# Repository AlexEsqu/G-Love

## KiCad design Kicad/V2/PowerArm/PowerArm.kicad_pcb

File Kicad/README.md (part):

https://app.notion.com/p/G-Love-Module-Electronique-06-26-42-Chips-371a25cc104180e3b6d8d438b70a2ca8

# Presentation

[G-Love] est un projet de conception d’un système de vêtement électronique (wearable) porté sur les bras., intégrant des bandes LEDSs RGB réactives à l’environnement et aux mouvements du porteur. (acceleration, flexion, pression)

Le système se présente sous forme de gant relié à une manchette d’avant-bras parcourus de capteurs et de LEDs. Un capteur sur le poignet permet de naviguer entre les modes.

---

# Table des matieres

---

# 1.Manuel d’utilisation

## Interactions

- Sur flexion / pression d’un doigt : animation localisée sur le segment correspondant
- Mouvement brusque du bras : traînée lumineuse, onde ?
- Orientation du bras : dégradé de couleur selon l’axe
- Bonus DMX : LEDs pilotees par reception DMX / Gestion d’une scene en transmission DMX

## Parametrage

- Pression bracelet : changement de mode pour passer d’un preset a l’autre
- Switch : pour demarrer avec ou sans feature LEDs
- Calibrage : via proximite aimant ou combinaison mouvement ?
- Bonus Touchscreen : Changer de mode / couleur

## Demarrage

Un utilisateur devra passer par une étape de calibration pour sa première utilisation du gant (longueur du bras et des doigts, amplitude de mouvement, calibration des senseurs…).
Mais les utilisations suivantes ne devraient pas nécessiter de vraie calibration, placer une nouvelle position d’origine au plus.

## Résumé

Les senseurs du gant devraient permettre de mesurer en temps réel la position de la main dans l’espace, la flexion des doigts, et les contacts avec le bout des doigts.

Les differents capteurs utilisés simultanément devraient permettre a l’utilisateur de déclencher plusieurs effets lumineux sur le display led, avec des combinaisons additives d’effets (mouvement + position des doigts X != mouvement + position Y != mouvement seul)

Ces mesures peuvent aussi être transmises en temps réel à une autre machine (à définir) pour lier ces mesures d’inputs à d’autres effets.

# 2.Features

---

## Mandatory

- 5 Ruban LED adressable sur les doigts, réagissant individuellement
- Interaction sur flexion d’un doigt (capteur flex a chaque doigt)
- Interaction sur pression du bout d’un doigt (capteur pression au bout de chaque doigt)
- Interaction sur :
    - mouvement de la main
    - l’orientation de la main
- Transmission coordonnée dans l’espace en temps réel par UART (précision dans la limite du matériel accessible avec le budget : plusieurs IMU, ou IMU plus précis, balise et triangulation…)
- Surface avant-bras LED adressable 16x16 / 16x64 (dans limite budget)
- Interaction sur l’avant bras (capteur pression)
- Envoi des donnees en USB via bridge USB to UART
- Système de reset des positions/mouvements (simple bouton ou combinaison d’input). Peut être nécessaire suivant le fonctionnement du capteur et la longueur d’utilisation.
- Système de calibration capable définir nouvelle origine (point 0,0,0) , sans reset tout le système. (si la calibration a été faite, un reset complet de la machine peut etre rattrappe en 2secondes si l’utilisateur garde une position de repos)

    Définir amplitude max du bras (bras tendu, leve, a plat sur les cuisses)

- Gestion embarquée de la chaleur des LEDs par capteur température et optimisation software ; utiliser des techno type textile conducteur, ??? pour permettre PLUS DE LED

## Bonus

#### Communication

- Interaction entre 2 gants dans le meme espace via coordonnees transmises en USB

#### TouchScreen

- Bonus: Touchscreen ou autre système d’input pour changer de mode/paramètres.

    Peut etre utile pour changer plus facilement les options pendant l‘utilisation de l’objet. Et pour visualiser les paramètres actuels sans trop perturber le display principal de l’objet.

#### DMX

- Bonus: Transmission DMX via driver RS-485 (MAX485 + XLR DMX)

    +Note: émission de format DMX probablement ingérable, réception semble plus réaliste.

#### FingerTip

- Bonus: Module Plug and Play HEARTBEAT capteur de pouls
- Bonus: Module Plug and play PISTODOIGT en infrarouge pour jouer au laser tag avec un doigt canon et le flex d’un autre doigt pour la gâchette  🔫
- Super Bonus : Module Plug and Play CURSOR permettant de dessiner en 3D ; Captation suffisamment précise pour dessiner un 42 lisible dans l’espace d’un 1m3

---

# 3. Schema fonctionnel

!Schema Fonctionnel.png

TO DO:
- formes logique
- légende
- ajouter ref compo

---

# 4. Matériel et protocoles

- **Microcontrôleurs relies UART** :
    - ATmega328P
    - ATmega32U4 (1 controleur principal pour les gouverner tous)
- **Bandes LEDs RGB** : WS2812B ou APA102 le long des doigts et panneau LEDs sur l’avant-bras
- **Capteurs** :

    **ADC** protocole **: Flex sensors** pour la flexion (duh), **FSR** (force-sensing resistor) pour la pression des doigts via multiplexeur CD4067

    **SPI / I2c** protocole **: IMU** (inertial measurement unit) pour accéléromètre + gyroscope,

    **Proximité** : Capteur Hall digital A3144

- **Support** : PCB Flex et PCB rigides avec segments flexibles entre chaque
- **Microcontrôleurs relies en UART** :
    - **ATmega328P (**main**)**
    - **ATmega2561** (avant-bras)
- **Capteurs** :

    **ADC** via multiplexer CD4067 **:**

    - **Flex sensors** pour la flexion des doigts
    - **FSR** (force-sensing resistor) pour la pression des doigts

    **I2C : IMU** (inertial measurement unit) pour accéléromètre + gyroscope

    **Digital I/O** :

    - **Capteur** Hall digital A3144
    - **bandes LEDs RGB** APA102 le long des doigts et panneau LEDs sur l’avant-bras
- **HeatSensor :** Utilisation de Thermistance NTC (negative temperature coefficient = la résistance diminue lorsque la température augmente), placé là où il y a le plus de variation de chaleur possible (rubans LED) avec de la colle thermique pour mieux capté la chaleur et recouvert d’un ruban Kapton pour isolé de l’air ambiant

- **Bonus SPI/I2C** : touchscreen, **GC9A01** est la puce qui contrôle l'affichage de l'écran et communique en SPI et **CST816D** est la puce qui contrôle la détection du tactile, communique en I2C
    - En sortie (Affichage - GC9A01) :
        - Afficher le mode d'interaction actuel (ex: "Mode DMX", "Mode Laser Tag")
        - Afficher des retours visuels lors de l'étape de calibration
    - En entrée (Saisie tactile - CST816D) :
        - Changement de mode: changement de mode pour différent interaction prédefini
        - Parametrage de couleurs: afficher une roue chromatique sur l'écran, permettant à l'utilisateur de sélectionner directement au doigt la couleur de base de ses bandes LED.
        - Bouton de secours / de reset: permet de déclencher manuellement un recalibration ou un “reset” en appuyant sur un bouton
- **Bonus UART** : USB
- **Bonus UART** : DMX
- **Support** : PCB Flex et PCB rigides avec segments flexibles entre chaque

## SPI (**Serial Peripheral Interface**)

SPI est un protocole ultra-rapide avec 4 fils : MOSI, MISO, SCK, CS. Fonctionnant sur une architecture de type master/slave, il permet des transferts de données bidirectionnels simultanenent  sans ralentir le microcontrôleur principal.

La synchronisation des échanges est assuré par un signal d’horloge généré exclusivement par le microcontroleur configuré en maitre

Le bus SPI repose sur l’utilisation de quatre lignes de signaux:

- SCK(Serial Clock) : Signal d’horloge generé par le maitre, il cadence le rythme de transmission des bits de données
- MOSI(Master Out Slave In) : Ligne de données unidirectionelle transportant les informations du maitre vers le slave
- MISO(Master In Slave Out) : ligne de données unidirectionelle transportant les informations du slave vers le maitre
- CS / SS (Chip Select / Slave Select) : Ligne d’activation dédié a chaque composant esclave, ce signal est actif a l’etat bas (0V), tant que le signal d’un esclave est haut, celui ci ignore le bus SPI et libere la ligne MISO
- Composant : Ruban LED APA102 (avant-bras).
    - **Le Maître :** L'ATmega328P est le maître du bus SPI
    - **Esclave :** Bandes LEDs APA102
    - **L'Usage :** Mise à jour à très haute fréquence de la matrice visuelle de l'avant-bras
    - **Câblage** : Utilise le D11(MOSI - Données) et D13 (SCK - Horloge)
- Composant : Ecran GC9A01
    - **Le Maitre** : L’ATMega2561 est le maitre du bus SPI
    - **Esclave :** L’écran GC9A01,
    - **L'Usage :** Le protocole SPI est un protocole assez rapide pour travailler et rafraichir un écran de 240x240pixels
    - **Cablage** : PB1(SCK - Horloge), PB2 (MOSI - Données), PB0 (SS/CS - Selection de l’ecran)

Les LED WS2812B utilise un protocole propriétaire de communication monofil, l’envoi des données à ces LED peut bloquer l’execution du programme et desactive les interruption du microcontrolleur

En choisissant les LED APA102 fonctionnant en SPI, la transmission de données est cadencée par la ligne d’horloge matérielle (SCK).  L’ATMega328P peut rafraichir l’affichage des LED sans aucune contrainte de temps grace au protocole SPI, lui permettant de simultanément et sans latences les capteurs

L’utilisation du protocole SPI pour l’affichage de l’ecran du TouchScreen permet aussi d’atteindre un taux de rafaichissement d’écran plus élevé et fluide avec 8MHz avec l’atm2561 contre 400kHz en I2C

## I2C **(Inter-Integrated Circuit)**

Le protocole I2C est un standard de communication bidirectionnel, il repose sur un principe d’adressage logiciel et permet de facilement reliée un microcontrolleur et différents circuits.

Contrairement au SPI qui necessite une ligne individuelle (Chip Select) par peripherique, le protocole I2C permet de connecter plusieurs dizaines de composants en parallele sur seulement deux lignes de communication:

- SCL (Serial Clock) : Signal d’horloge generé par le maitre pour cadencer la transmission des bits
- SDA (Serial Data) : Ligne de données bidirectionnelle transportant alternativement les informations du maitre vers le slave, et du slave vers le maitre

Adressage Unique: Chaque esclave I2C possède une adresse codée en binaire définie en usine ou par configuration matérielle. Le maitre commence chaque interaction en envoyant l’adresse du composant visé sur le fil SDA. Seul le composant possédant cette adresse répond, les autres ignorant la suite des paquets.

- Composant : ICM-42699-P
    - **Le Maitre** : L’ATMega328P est le maitre du bus I2C
    - **Esclave :**  ICM-42699-P
    - **L'Usage :** Le protocole I2C est
    - **Cablage** : SDA et SDL
- Composant : ecran tactile CST816D
    - **Le Maitre** : L’ATMega2561 est le maitre du bus I2C
    - **Esclave :**  CST816D
    - **L'Usage :** Le protocole I2C est
    - **Cablage** : SDA et SDL

L’adoption de l’I2C pour la gestion des capteurs de position et l’interaction tactile du TouchScreen:

- Minimisation de l’encombrement du cablage
    - L’I2C permet de connecter l’IMU et l’ecran tactile en n’utilsaint que 2 lignes de données, evitant de saturer les pins des micronctrolleur et d’alourdir le cablage flexible du bras
- Echange de données plus lent
    - Contraireemnt à l’écran LCD, le tactile et l’IMU ne transmettenet que de petit paquets de données, la vitesse de l’I2C est suffisante pour l’echange de donnée

## UART (Universal Asynchronous Receiver-Transmitter)

## ADC

## DIGITAL I/O

---

# 5. Pinout

## ATmega328p — Concentrateur capteurs + APA102

### MANDATORY

#### ALIMENTATION & PROGRAMMATION

| Pin | Composant | Signal / rôle | Protocole |
| --- | --- | --- | --- |
| **VCC / GND** | Alim | 5V — 100nF par paire VCC/GND | PWR |
| **RESET** | Reset | Pull-up 10kΩ vers VCC | Reset |

---

#### CRYSTAL OSCILLATOR

| Pin | Composant | Signal / rôle | Protocole |
| --- | --- | --- | --- |
| **B6 / XTAL1** | Crystal / Oscillator | External Clock |  |
| **B7 / XTAL2** | Crystal / Oscillator | External Clock |  |

---

#### ADC + MULTIPLEXER

| Pin | Composant | Signal / rôle | Protocole |
| --- | --- | --- | --- |
| **C0** | CD4067 S0 | Sélection canal multiplexeur | Digital |
| **C1** | CD4067 S1 | Sélection canal multiplexeur | Digital |
| **C2** | CD4067 S2 | Sélection canal multiplexeur | Digital |
| **C3** | CD4067 S3 | Sélection canal multiplexeur | Digital |
| **ADC7** | CD4067 output | Multiplex FSR doigts + Flex | ADC |
| **ADC6** | FSR 402 poignet | Capteur de force | ADC |

---

#### I2C IMU

| Pin | Composant | Signal / rôle | Protocole |
| --- | --- | --- | --- |
| **C4 / SDA** | ICM-42688 | IMU SDA | I2C |
| **C5 / SCL** | ICM-42688 | IMU SCL | I2C |

---

#### GPIO Hall

| Pin | Composant | Signal / rôle | Protocole |
| --- | --- | --- | --- |
| **D6** | A3144 Hall | Capteur magnétique | GPIO |

---

#### SPI LEDs

| Pin | Composant | Signal / rôle | Protocole |
| --- | --- | --- | --- |
| **B4** | APA102 ruban #1 | CS ruban 1 | GPIO CS |
| **B3 / MOSI** | APA102 DI (tous) | Data SPI — bus commun | SPI HW |
| **B5 / SCK** | APA102 CI (tous) | Clock SPI — bus commun | SPI HW |

---

#### BONUS UART

| Pin | Composant | Signal / rôle | Protocole |
| --- | --- | --- | --- |
| **D0 / RX** | ATmega2561 | RX ← TX du 2561 | UART |
| **D1 / TX** | ATmega2561 | TX → RX du 2561 | UART |

---

#### RECAP

| Pin | Composant | Signal / rôle | Protocole |
| --- | --- | --- | --- |
| **C0** | CD4067 S0 | Sélection canal multiplexeur | Digital |
| **C1** | CD4067 S1 | Sélection canal multiplexeur | Digital |
| **C2** | CD4067 S2 | Sélection canal multiplexeur | Digital |
| **C3** | CD4067 S3 | Sélection canal multiplexeur | Digital |
| **ADC7** | CD4067 output | Multiplex FSR doigts + Flex | ADC |
| **D6** | A3144 Hall | Capteur magnétique | Digital IN |
| **B4** | APA102 ruban #1 | CS ruban 1 | GPIO CS |
| **B3 / MOSI** | APA102 DI (tous) | Data SPI — bus commun | SPI HW |
| **B5 / SCK** | APA102 CI (tous) | Clock SPI — bus commun | SPI HW |
| **ADC6** | FSR 402 poignet | Capteur de force | ADC |
| **C4 / SDA** | ICM-42688 | IMU SDA | I2C |
| **C5 / SCL** | ICM-42688 | IMU SCL | I2C |
| **B6 / XTAL1** | Crystal / Oscillator | External Clock |  |
| **B7 / XTAL2** | Crystal / Oscillator | External Clock |  |
| **VCC / GND** | Alim | 5V — 100nF par paire VCC/GND | PWR |
| **RESET** | Reset | Pull-up 10kΩ vers VCC | Reset |

| **D0 / RX** | ATmega2561 | RX ← TX du 2561 | UART |
| --- | --- | --- | --- |
| **D1 / TX** | ATmega2561 | TX → RX du 2561 | UART |

---

## BONUS A FINIR

## ATmega2561 — Display + bus + périphériques

#### ALIMENTATION & PROGRAMMATION

| Pin | Composant | Signal / rôle | Protocole |
| --- | --- | --- | --- |
| **VCC / GND** | Alim | 5V — 100nF par paire VCC/GND | PWR |
| **RESET** | Reset | Pull-up 10kΩ vers VCC | Reset |

---

#### CRYSTAL OSCILLATOR

| Pin | Composant | Signal / rôle | Protocole |
| --- | --- | --- | --- |
| **XTAL1** | Crystal / Oscillator | External Clock |  |
| **XTAL2** | Crystal / Oscillator | External Clock |  |

#### UART0 — Lien vers ATmega328p

| Pin | Composant | Signal / rôle | Protocole |
| --- | --- | --- | --- |
| **E0** | ATmega328p | RX ← TX du 328p | UART0 |
| **E1** | ATmega328p | TX → RX du 328p | UART0 |

#### UART1 — USB via FTDI FT232R / Bus RS-485 via MAX487

| Pin | Composant | Signal / rôle | Protocole |
| --- | --- | --- | --- |
| **D2 / TXD2** | 74HC4053 | TX → FTDI RX / MAX487 DI | UART1 |
| **D3 / RXD2** | 74HC4053 | RX ← FTDI TX (1kΩ série) / MAX487 RO | UART1 |
| **D5** | 74HC4053 | Switch Digital | GPIO |
| **D4** | GPIO | MAX487 DE + ~RE (liés ensemble) | GPIO |

#### **Module TouchScreen (GC9A01 + CST816D) avec LevelShifter TXS0108EPWR**

| Pin | Composant | Signal / rôle | Protocole |
| --- | --- | --- | --- |
| PB0 | ~SS / CS | LCD CS | GPIO CS |
| PB1 | SCK | SCLK | SPI |
| PB2 | MOSI | MOSI | SPI |
| PB3 | MISO | MISO | SPI |
| PB4 | GPIO | LCD DC / RS | GPIO |
| PB5 | GPIO | LCD RST | GPIO |
| PD0 | SCL I2C | Touchscreen SCL | I2C |
| PD1 | SDA I2C | Touchscreen Data | I2C |
| PE4 | INT4 | Touchscreen Interrupt | I2C |

#### Plug & play (pouls / IR) + switch pression

| Pin | Composant | Signal / rôle | Protocole |
| --- | --- | --- | --- |
| **PE2** | INT2 | Capteur pouls / IR — signal data | INT ext. |
| **PE3** | GPIO | Détection présence connecteur (pull-up) | GPIO |
| **PE4** | INT4 | Switch pression — interrupt | INT ext. |

# 6. BOM

| Component | QTY | Prix unitaire (€) | Prix total (€) | Fournisseur |
| --- | --- | --- | --- | --- |
| **ATMega328P** | 1 | 2,26 | 2,26 | https://www.digikey.fr/fr/products/detail/microchip-technology/ATMEGA328P-AU/1832260 |
| **ATMega2561** | 1 | 13,17 | 13,17 | https://www.digikey.fr/fr/products/detail/microchip-technology/ATMEGA2561-16AU/735457 |
| **Interlink FSR 400 short (FSR doigt)** | 5 | 4,886 | 24,43 | https://www.digikey.fr/fr/product-highlight/i/interlink/fsr-400-round-force-sensing-resistor |
| **Spectra Symbol SEN-10264 2.2” (Flex Sensor)** | 4 | 10,16 | 40,64 | https://www.digikey.fr/fr/products/detail/sparkfun-electronics/10264/17829611 |
| **Interlink FSR 402 medium (FSR avant bras)** | 1 | 6,05 | 6,05 | https://www.digikey.fr/en/product-highlight/i/interlink/fsr-402-round-force-sensing-resistor |
| **Multiplexer CD4067**  | 1 | 0,79 | 0,79 | https://www.digikey.fr/fr/products/detail/texas-instruments/CD4067BM96/1691267 |
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
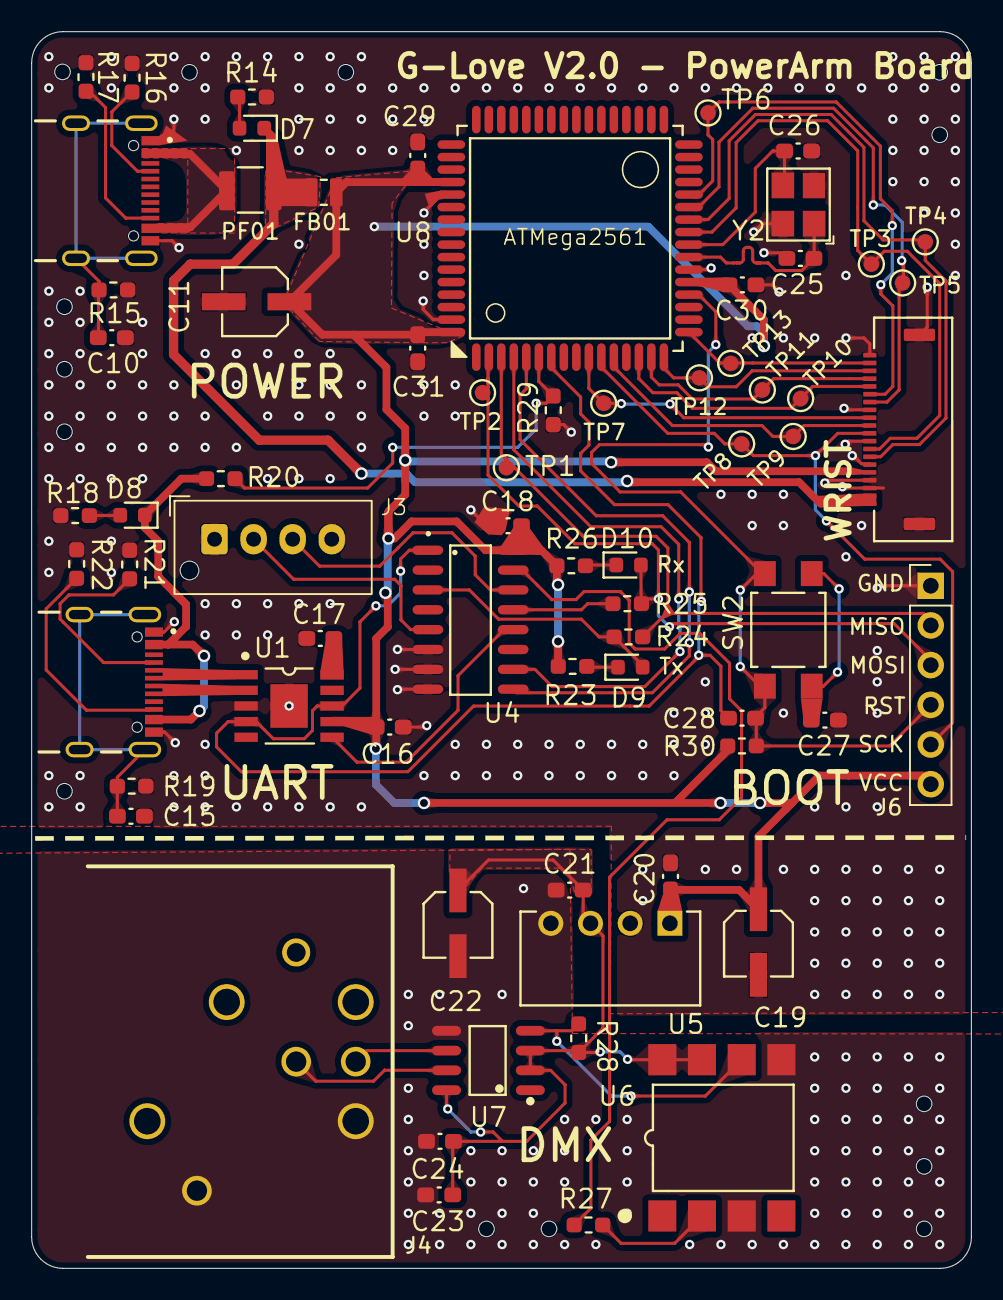
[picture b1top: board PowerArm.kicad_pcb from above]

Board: 2 copper layers, 60.1 x 79.1 mm, 69 parts (0 on the bottom side), 50 nets.

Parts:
C10: 10n; Capacitor_0603
C11, C19, C22: 4.7uF; Capacitor_Electrolytic
C15: 10nF; Capacitor_0603
C16, C17, C18, C20, C21, C23, C24, C27, C28, C29, C30, C31: 100nF; Capacitor_0603
C25, C26: 12pF; Capacitor_0603
D7: RED; LED
D8: GREEN; LED
D9, D10: YELLOW; LED
FB01: FERRITE BEAD
J1: JST_Connector_To_Wrist_Board; conn_zif_20x0.5mm
J2: USB Connector to Computer; USB_C_Receptacle_GCT_USB4105-xx-A_16P_TopMnt_Horizontal
J3: JST_Connector_To_Other_Glove; Conn_JST_4x2.50mm
J4: XLR5_Ground; XLR5_Connector_Female_CONN-TH_NC5FAH
J5: USB Connector to Powerbank; USB_C_Receptacle_GCT_USB4105-xx-A_16P_TopMnt_Horizontal
J6: PinHeader_1x06_P2.54mm_Vertical
PF01: POLYMER FUSE
R14, R18, R20, R23, R24, R25, R26: 1k; Resistor_0603
R15, R19: 1M; Resistor_0603
R16, R17: 5.1k; Resistor_0603
R21, R22: 5.1K; Resistor_0603
R27: 330R; Resistor_0603
R28: 4.7k; Resistor_0603
R29: 10k; Resistor_0603
R30: 10kΩ; Resistor_0603
SW2: SW_SPST_TL3305A
TP1, TP2, TP3, TP4, TP5, TP6, TP7, TP8, TP9, TP10, TP11, TP12, TP13: TestPoint_Pad_D1.0mm
U1: CH340K
U4: 74HC4052
U5: B0505S-1W1; B0505S
U6: 6N137
U7: MAX485E; MAX485ED
U8: ATMEGA2561-16AU; ATMega2561
Y2: 16MHz; Crystal_16MHz

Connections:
/ATMega2561/2561_MOSI: J1.11 (MOSI), TP9.1, U8.12 ((MOSI/PCINT2)_PB2)
/ATMega2561/2561_MUX_SELECT_A: U4.10 (A), U8.4 (PE2_(XCK0/AIN0))
/ATMega2561/2561_MUX_SELECT_B: U4.9 (B), U8.5 (PE3_(OC3A/AIN1))
/ATMega2561/2561_RXD1: J1.14 (2561_RX), TP5.1, U8.27 ((RXD1/INT2)_PD2)
/ATMega2561/2561_SCL: J1.8 (SCL), TP3.1, U8.25 ((SCL/INT0)_PD0)
/ATMega2561/2561_SCREEN_DC: J1.16 (SCREEN_DC), TP10.1, U8.14 ((OC2A/_PCINT4)_PB4)
/ATMega2561/2561_SCREEN_RESET: J1.17 (SCREEN_RESET), TP11.1, U8.15 ((OC1A/PCINT5)_PB5)
/ATMega2561/2561_SDA: J1.7 (SDA), TP4.1, U8.26 ((SDA/INT1)_PD1)
/ATMega2561/2561_SS: J1.12 (SS), TP7.1, U8.10 ((~SS/PCINT0)_PB0)
/ATMega2561/2561_TOUCH_INT: J1.18 (TOUCH_INT), TP12.1, U8.16 ((OC1B/PCINT6)_PB6)
/ATMega2561/2561_TOUCH_RESET: J1.19 (TOUCH_RESET), TP13.1, U8.17 ((OC0A/OC1C/PCINT7)_PB7)
/ATMega2561/2561_TXD1: J1.15 (2561_TX), TP6.1, U8.28 ((TXD1/INT3)_PD3)
/ATMega2561/2561_USB1_INT: R20.2, R29.2, U8.6 (PE4_(OC3B/INT4))
/ATMega2561/DTR: C28.2, U1.4 (~DTR), U1.8 (TXD), U4.1 (Y0), U8.7 (PE5_(OC3C/INT5))
/ATMega2561/MCU_2561_RESET: C28.1, J6.4, R30.1, SW2.2, U8.20 (~RESET)
/ATMega2561/MISO_BOOT_2561: J6.2, R24.2, TP1.1, U8.3 (PE1_(TXD0/PDO))
/ATMega2561/MOSI_BOOT_2561: D10.2 (K), J6.3, R25.2, TP2.1, U8.2 (PE0_(RXD0/PCINT8/PDI))
/ATMega2561/SCK_BOOT_2561: J1.10 (SCK), J6.5, TP8.1, U8.11 ((SCK/PCINT1)_PB1)
/Data/DMX/TX_DMX: R27.1, U4.15 (X2)
GND: C10.2, C11.2, C15.2, C16.1, C17.1, C18.2, C19.2, C20.2, C25.2, C26.1, C27.1, C29.2, C30.2, C31.2, J1.3 (GND), J1.4 (GND), J1.6 (GND), J1.9 (GND), J1.13 (GND), J1.20 (GND), J3.1 (GND), J3.4 (GND), J6.1, R14.1, R15.2, R16.1, R17.1, R18.1, R19.2, R21.2, R22.2, R29.1, U1.3 (GND), U1.11 (GND), U4.6 (INH), U4.7 (VEE), U4.8 (GND), U5.2 (GND), U8.22 (GND_2), U8.53 (GND), U8.63 (GND_3), Y2.2 (G), Y2.4 (G)
unnamed: C27.2, SW2.1
unnamed: D7.2 (K), R14.2
unnamed: D8.2 (K), R18.2
unnamed: D9.1 (A), R23.2
unnamed: D9.2 (K), R24.1, U4.3 (Y)
unnamed: D10.1 (A), R26.2
unnamed: J2.A5 (CC1), R21.1
unnamed: J2.B5 (CC2), R22.1
unnamed: C15.1, J2.SH (SHIELD), R19.1
unnamed: J3.3 (Rx), U4.14 (X1)
unnamed: J3.2 (Tx), U4.5 (Y1)
unnamed: C21.2, C22.2, C23.1, C24.1, J4.1, J4.G, U5.4 (0V), U6.3 (C), U6.5 (GND), U7.5 (GND)
unnamed: J4.2, U7.7 (B)
unnamed: J5.A5 (CC1), R16.2
unnamed: J5.B5 (CC2), R17.2
unnamed: C10.1, J5.SH (SHIELD), R15.1
unnamed: U1.6 (RXD), U4.12 (X0)
unnamed: J2.A6 (D-), J2.B7 (D-), U1.1 (UD+)
unnamed: J2.A7 (D+), J2.B6 (D+), U1.2 (UD-)
unnamed: C17.2, U1.10 (V3)
unnamed: R25.1, U4.13 (X)
unnamed: C21.1, C22.1, C23.2, C24.2, R28.2, U5.3 (+VO), U6.7 (EN), U6.8 (VCC), U7.2 (~RE), U7.3 (DE), U7.8 (VCC)
unnamed: R27.2, U6.2 (A)
unnamed: R28.1, U6.6 (VO), U7.4 (DI)
unnamed: J4.3, U7.6 (A)
unnamed: C26.2, U8.24 (XTAL1), Y2.3
unnamed: C25.1, U8.23 (XTAL2), Y2.1
VBUS: D8.1 (A), PF01.1, R20.1
VCC: C11.1, C16.2, C18.1, C19.1, C20.1, C29.1, C30.1, C31.1, FB01.2, J1.5 (5V), J6.6, R23.1, R26.1, R30.2, U1.7 (VCC), U4.16 (VCC), U5.1 (VIN), U8.21 (VCC_2), U8.52 (VCC), U8.64 (AVCC)
VCCL: D7.1 (A), FB01.1, J1.1 (5V_LED), J1.2 (5V_LED), PF01.2

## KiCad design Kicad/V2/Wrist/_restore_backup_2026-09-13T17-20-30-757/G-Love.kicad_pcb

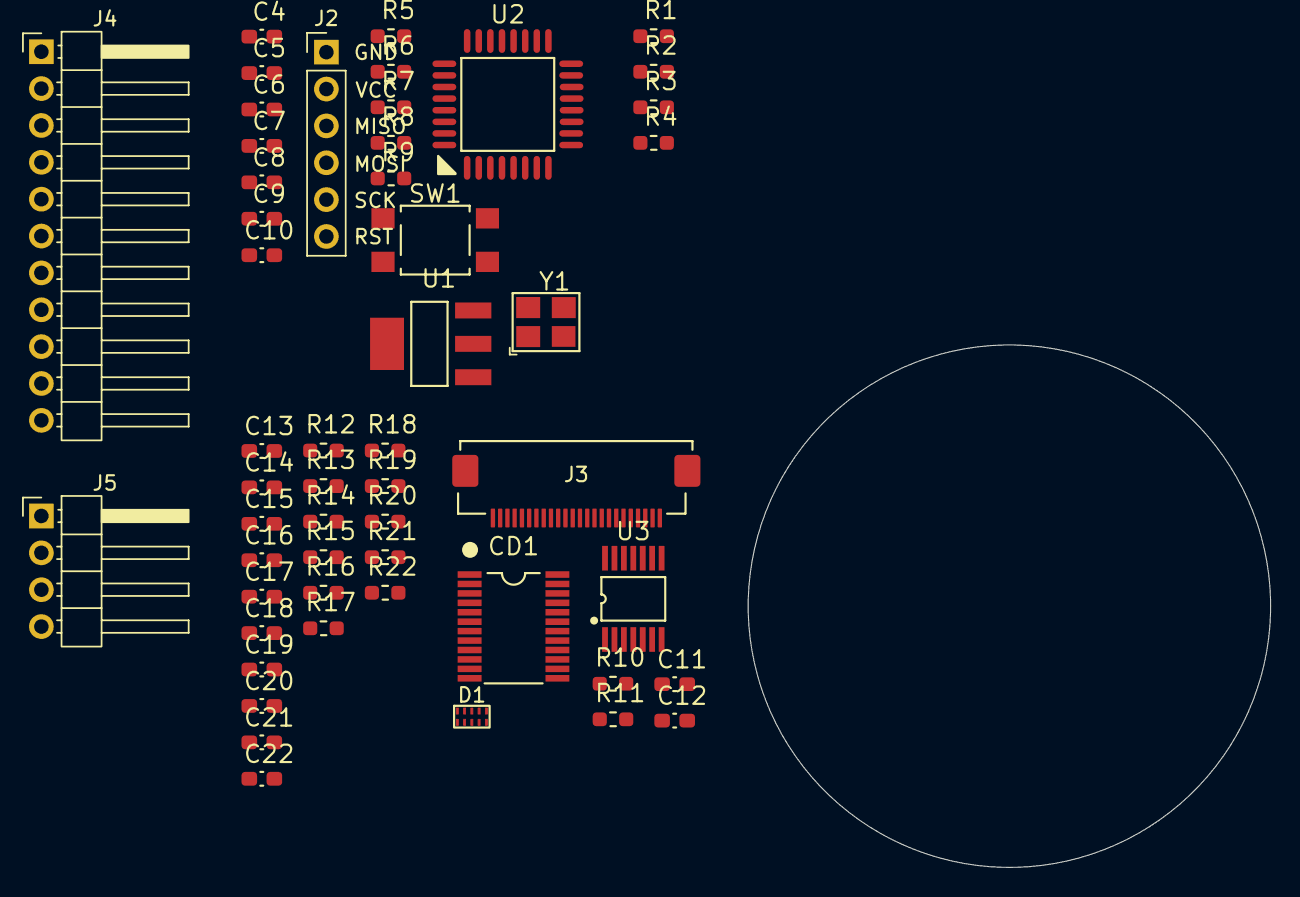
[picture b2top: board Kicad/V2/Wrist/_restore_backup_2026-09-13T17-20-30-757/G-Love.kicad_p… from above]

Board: 2 copper layers, 36.0 x 36.0 mm, 52 parts (0 on the bottom side), 37 nets, no tracks yet.

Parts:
C4, C5, C6, C7, C8, C11, C12: 100nF; Capacitor_0603
C9, C10: 12pF; Capacitor_0603
C13, C14, C15, C16, C17, C18, C19, C20, C21, C22: 10nF; Capacitor_0603
CD1: CD4097B
D1: TVS_DIODE
J2: PinHeader_1x06_P2.54mm_Vertical
J3: FPC_CONNECTOR_24
J4: PinHeader_1x11_P2.54mm_Horizontal
J5: PinHeader_1x04_P2.54mm_Horizontal
R1, R2, R8, R9: 2.2kΩ; Resistor_0603
R3, R4, R10, R11: 2.2K; Resistor_0603
R5, R13, R14, R15, R16, R17, R18, R19, R20, R21, R22: 10kΩ; Resistor_0603
R6, R7: 330R; Resistor_0603
R12: 10K; Resistor_0603
SW1: SW_SPST_TL3305A
U1: AMS1117
U2: ATMega328P; ATMega328P-AU
U3: TXS0104E; TXS0104EPWR
Y1: 16MHz; Crystal_16MHz

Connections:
+3.3V: C12.2, J3.8 (3.3V), J5.1, R10.2, R11.2, U1.2 (Vout), U3.1 (V_{CCA})
/ATmega328p/328P_ADC_MUX_INH: CD1.13 (INHIBIT), U2.26 (ADC3/PCINT11/PC3)
/ATmega328p/328P_ADC_MUX_SELECT_A: CD1.10 (A), U2.25 (ADC2/PCINT10/PC2)
/ATmega328p/328P_ADC_MUX_SELECT_B: CD1.11 (B), U2.23 (ADC0/PCINT8/PC0)
/ATmega328p/328P_ADC_MUX_SELECT_C: CD1.14 (C), U2.24 (ADC1/PCINT9/PC1)
/ATmega328p/328P_ADC_X_OUT: CD1.1 (X_OutIn), U2.22 (ADC7)
/ATmega328p/328P_ADC_Y_OUT: CD1.17 (Y_OutIn), U2.19 (ADC6)
/ATmega328p/328P_I2C_IMU_SCL: R4.1, R8.1, U2.28 (SCL/ADC5/PCINT13/PC5), U3.12 (B2)
/ATmega328p/328P_I2C_IMU_SDA: R3.1, R9.1, U2.27 (SDA/ADC4/PSCINT12/PC4), U3.13 (B1)
/ATmega328p/MCU_328P_RESET: J2.4, R5.1, SW1.2, U2.29 (~RESET/PCINT14/PC6)
/ATmega328p/MISO_BOOT_328P: D1.2, J2.2, J3.5 (MOSI), R6.2
/ATmega328p/MOSI_BOOT_328P: J2.3, U2.16 (MISO/PCINT4/PB4)
/ATmega328p/SCK_BOOT_328P: D1.1, J2.5, J3.6 (SCK), R7.2
/FingerTip Modules/FingerTip_I2C_SCL: J4.5, J5.2, R1.1
/FingerTip Modules/FingerTip_I2C_SDA: J4.4, J5.3, R2.1
/Hand_Captors/hand_captors/FLEX_INDEX_IN: C16.1, CD1.8 (X_1), J3.16 (FLEX_INDEX), R16.1
/Hand_Captors/hand_captors/FLEX_LITTLE_IN: C22.1, CD1.5 (X_4), J3.23 (FLEX_LITTLE), R22.1
/Hand_Captors/hand_captors/FLEX_MIDDLE_IN: C18.1, CD1.7 (X_2), J3.19 (FLEX_MIDDLE), R18.1
/Hand_Captors/hand_captors/FLEX_RING_IN: C20.1, CD1.6 (X_3), J3.21 (FLEX_RING), R20.1
/Hand_Captors/hand_captors/FLEX_THUMB_IN: C14.1, CD1.9 (X_0), J3.14 (FLEX_THUMB), R14.1
/Hand_Captors/hand_captors/FORCE_INDEX_IN: C15.1, CD1.22 (Y_1), J3.15 (FSR_INDEX), R15.1
/Hand_Captors/hand_captors/FORCE_LITTLE_IN: C21.1, CD1.19 (Y_4), J3.22 (FORCE_LITTLE), R21.1
/Hand_Captors/hand_captors/FORCE_MIDDLE_IN: C17.1, CD1.21 (Y_2), J3.17 (FSR_MIDDLE), R17.1
/Hand_Captors/hand_captors/FORCE_RING_IN: C19.1, CD1.20 (Y_3), J3.20 (FORCE_RING), R19.1
/Hand_Captors/hand_captors/FORCE_THUMB_IN: C13.1, CD1.23 (Y_0), J3.13 (FSR_THUMB), R13.1
/Hand_Captors/hand_captors/HALL_IN: CD1.18 (Y_5), J3.12 (SW_HALL), R12.1
GND: C4.1, C5.1, C6.1, C7.1, C8.2, C9.1, C10.1, C11.2, C12.1, C13.2, C14.2, C15.2, C16.2, C17.2, C18.2, C19.2, C20.2, C21.2, C22.2, CD1.12 (VSS), D1.3, J2.1, J3.3 (GNDL), J3.4 (GNDL), J3.7 (GND), J3.11 (GND), J3.18 (GND), J3.24 (GND), J4.1, J5.4, R13.2, R14.2, R15.2, R16.2, R17.2, R18.2, R19.2, R20.2, R21.2, R22.2, U1.1 (GND), U2.3 (GND), U2.5 (GND), U2.21 (GND), U3.7 (GND), Y1.2 (G), Y1.4 (G)
unnamed: C7.2, SW1.1
unnamed: D1.5, J3.10 (SCL), R10.1, U3.3 (A2)
unnamed: D1.4, J3.9 (SDA), R11.1, U3.2 (A1)
unnamed: C4.2, U2.20 (AREF)
unnamed: R6.1, U2.15 (OC2A/MOSI/PCINT3/PB3)
unnamed: R7.1, U2.17 (SCK/PCINT5/PB5)
unnamed: C9.2, U2.7 (XTAL1/TOSC1/PCINT6/PB6), Y1.1
unnamed: C10.2, U2.8 (XTAL2/TOSC2/PCINT7/PB7), Y1.3
VCC: C5.2, C6.2, C8.1, C11.1, CD1.24 (VDD), J2.6, J4.11, R1.2, R2.2, R3.2, R4.2, R5.2, R8.2, R9.2, R12.2, U1.3 (Vin), U2.4 (VCC), U2.6 (VCC), U2.18 (AVCC), U3.14 (V_{CCB})
VCCL: J3.1 (VCCL), J3.2 (VCCL)

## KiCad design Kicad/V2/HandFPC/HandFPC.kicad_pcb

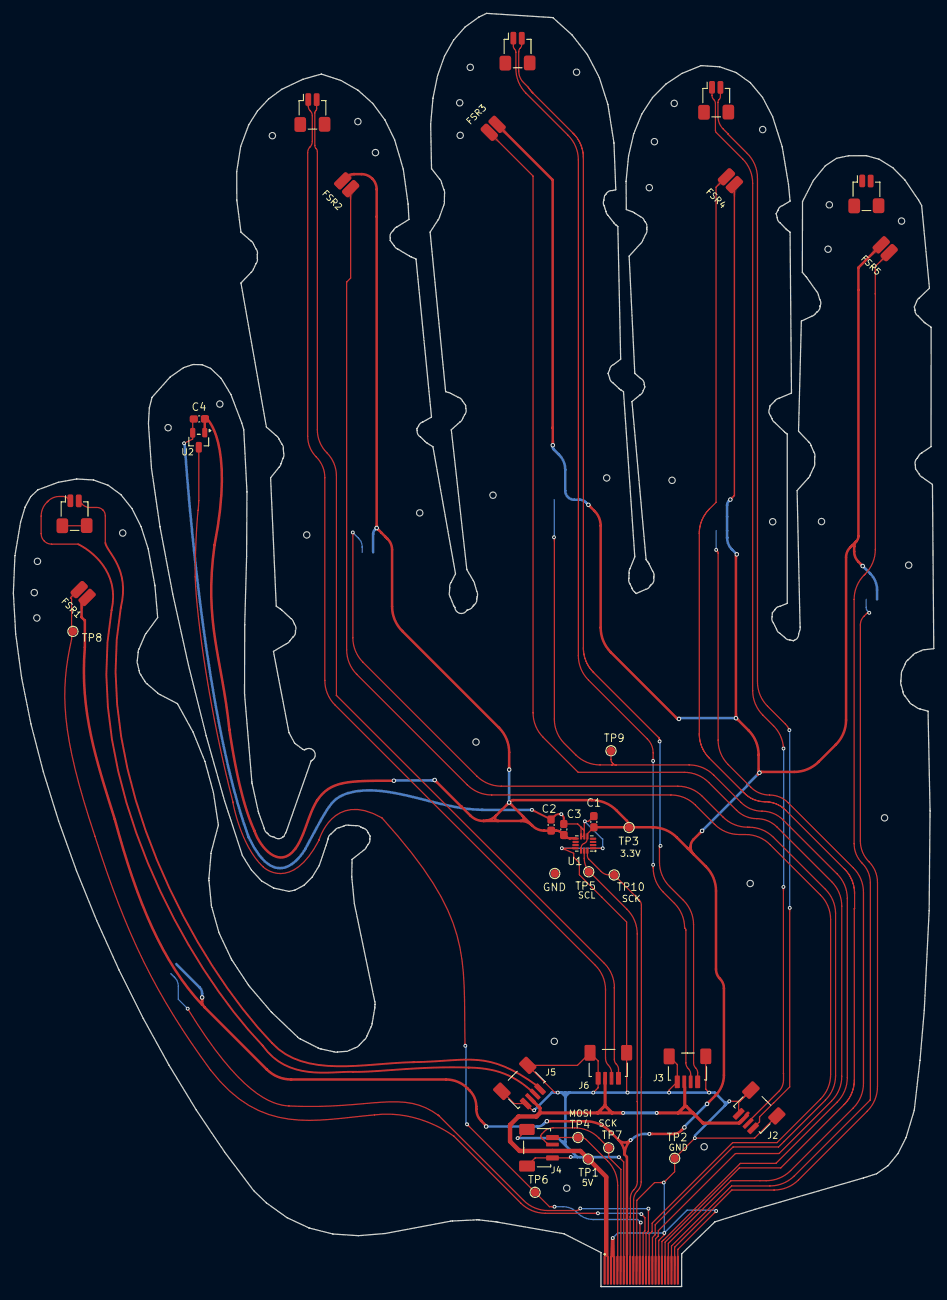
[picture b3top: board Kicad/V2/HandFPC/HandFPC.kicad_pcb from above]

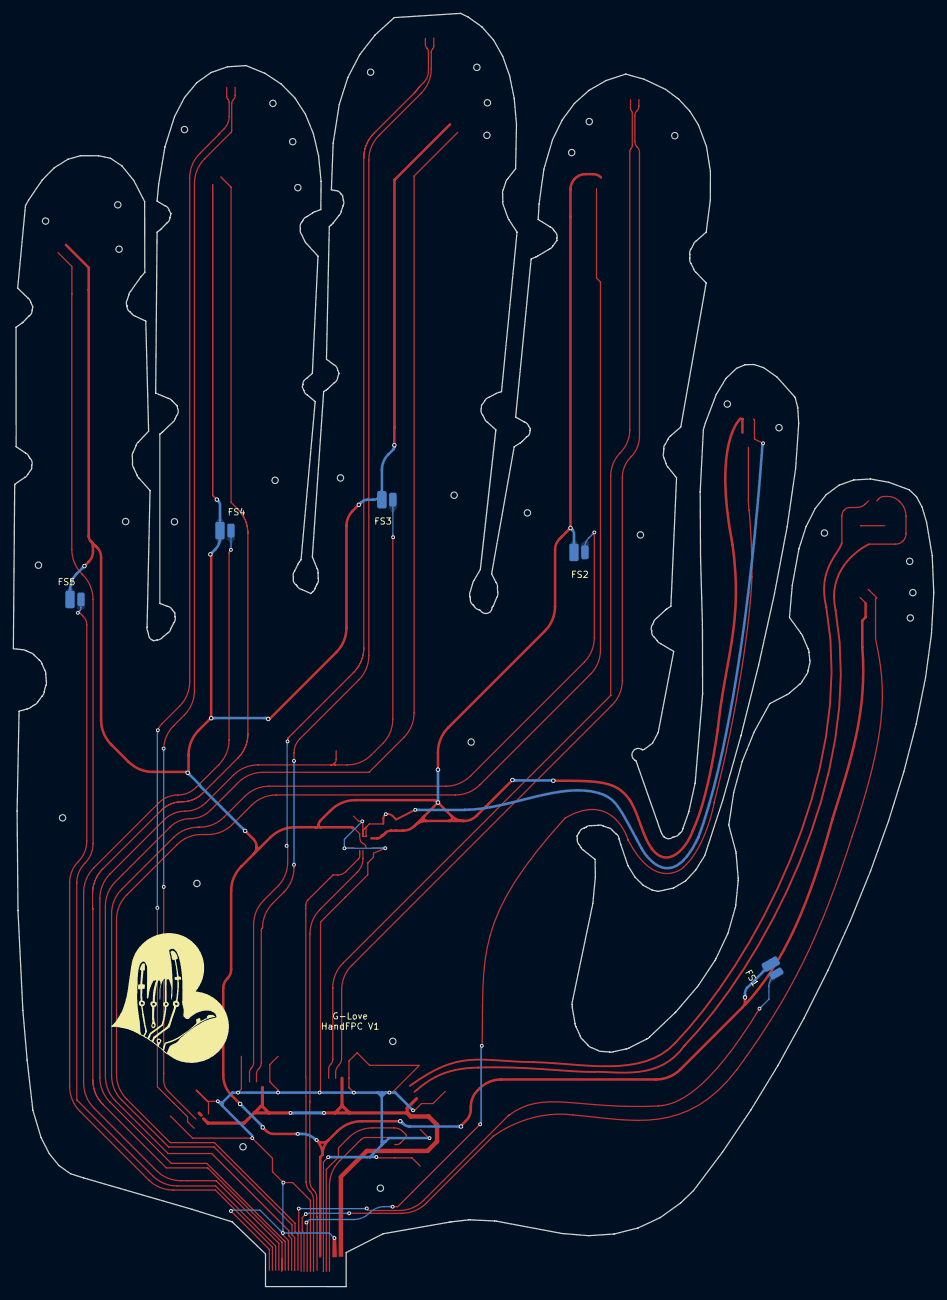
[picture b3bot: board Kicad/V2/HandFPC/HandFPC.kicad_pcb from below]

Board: 2 copper layers, 144.5 x 200.0 mm, 38 parts (5 on the bottom side), 26 nets.

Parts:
C1: 10nf; FPC_0603
C2: 2.2nF; FPC_0603
C3: 0.1nF; FPC_0603
C4: 100 nF; FPC_0603
FS1, FS2, FS3, FS4, FS5: FPC_FS
FSR1, FSR2, FSR3, FSR4, FSR5: FPC_FSR
GND: FPC_TestPoint
J1: FPC_Conn; FPC_Conn_24_GoldFinger
J2: JST_LED_SPI_In_Little; FPC_JST_Conn_4x1.00mm
J3: JST_LED_SPI_In_Ring; FPC_JST_Conn_4x1.00mm
J4: JST_LED_SPI_In_Thumb; FPC_JST_Conn_4x1.00mm
J5: JST_LED_SPI_In_Index; FPC_JST_Conn_4x1.00mm
J6: JST_LED_SPI_In_Major; FPC_JST_Conn_4x1.00mm
J7: JST_SPI_LED_Out_Thumb; FPC_JST_Conn_2x1.00mm
J8: JST_SPI_LED_Out_Index; FPC_JST_Conn_2x1.00mm
J9: JST_SPI_LED_Out_Major; FPC_JST_Conn_2x1.00mm
J10: JST_SPI_LED_Out_Ring; FPC_JST_Conn_2x1.00mm
J11: JST_SPI_LED_Out_Little; FPC_JST_Conn_2x1.00mm
TP1, TP2, TP3, TP4, TP5, TP6, TP7, TP8, TP9, TP10: FPC_TestPoint
U1: ICM-42688-P_I2C; FPC_ICM-42688-P
U2: Hall Sensor DRV5023; FPC_SOT_23

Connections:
5VL: J1.1 (5V), J1.2 (5V), J2.3, J3.3, J4.3, J5.3, J6.3, TP1.1
+3.3V: C1.2, C2.1, C3.1, C4.1, FS1.2, FS2.2, FS3.2, FS4.2, FS5.2, FSR1.2, FSR2.2, FSR3.2, FSR4.2, FSR5.2, J1.8 (3.3V), TP3.1, U1.5 (VDDIO), U1.8 (VDD), U1.12 (VDDIO), U2.1 (VCC)
/FSR_Index/TouchADC: FSR2.1, J1.15 (FSR_INDEX)
/FSR_Little/TouchADC: FSR5.1, J1.22 (FSR_LITTLE)
/FSR_Middle/TouchADC: FSR3.1, J1.17 (FSR_MIDDLE)
/FSR_Ring/TouchADC: FSR4.1, J1.20 (FSR_RING)
/FSR_Thumb/TouchADC: FSR1.1, J1.13 (FSR_THUMB), TP8.1
/FingerLED/LED_MOSI: J1.5 (MOSI), J4.1, TP4.1
/FingerLED/LED_SCK: J1.6 (SCK), J4.2, TP7.1
/Flex_Index/FlexADC: FS2.1, J1.16 (FLEX_INDEX)
/Flex_Little/FlexADC: FS5.1, J1.23 (FLEX_LITTLE)
/Flex_Middle/FlexADC: FS3.1, J1.19 (FLEX_MIDDLE), TP9.1
/Flex_Ring/FlexADC: FS4.1, J1.21 (FLEX_RING)
/Flex_Thumb/FlexADC: FS1.1, J1.14 (FLEX_THUMB)
/Hall Captor/Hall_Captor_GPIO: J1.12 (HALL), TP6.1, U2.3 (Output)
/IMU_1/IMU_I2C_SCL: J1.9 (SDA), TP5.1, U1.13 (AP_SCK)
/IMU_1/IMU_I2C_SDA: J1.10 (SCL), TP10.1, U1.14 (AP_SDA)
GND: C1.1, C2.2, C3.2, C4.2, J1.3 (GND), J1.4 (GND), J1.7 (GND), J1.11 (GND), J1.18 (GND), J1.24 (GND), J2.4, J2.5, J3.4, J3.5, J4.4, J4.5, J5.4, J5.5, J6.4, J6.5, TP2.1, U1.1 (AP_AD0), U1.6 (GND), U1.7 (RESV), U1.11 (RESV), U2.2 (GND)
unnamed: J3.1, J9.2
unnamed: J3.2, J9.1
unnamed: J5.1, J7.2
unnamed: J5.2, J7.1
unnamed: J6.1, J8.2
unnamed: J6.2, J8.1
unnamed: J2.2, J10.1
unnamed: J2.1, J10.2

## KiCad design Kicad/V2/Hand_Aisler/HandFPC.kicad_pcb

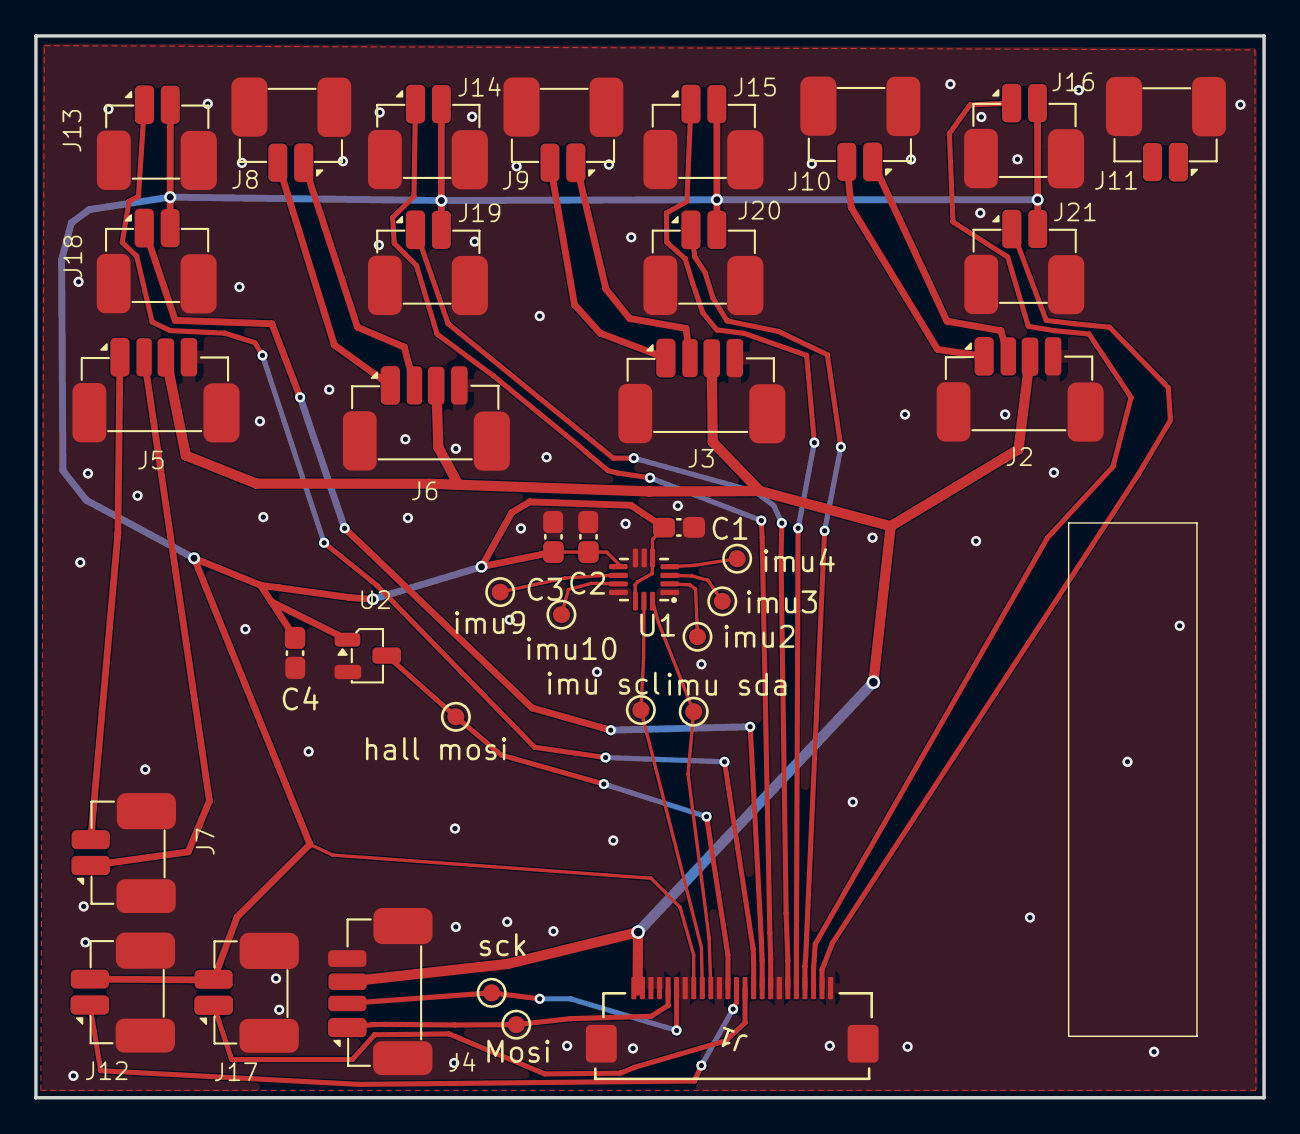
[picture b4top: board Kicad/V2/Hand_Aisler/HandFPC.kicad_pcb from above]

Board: 2 copper layers, 71.8 x 62.0 mm, 37 parts (0 on the bottom side), 26 nets.

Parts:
C1: 10nf; FPC_0603
C2: 2.2nF; FPC_0603
C3: 0.1nF; FPC_0603
C4: 100 nF; FPC_0603
J1: FPC_Conn; FPC_CONNECTOR_24
J2: JST_LED_SPI_In_Little; FPC_JST_Conn_GH_4x1.25mm
J3: JST_LED_SPI_In_Ring; FPC_JST_Conn_GH_4x1.25mm
J4: JST_LED_SPI_In_Thumb; FPC_JST_Conn_GH_4x1.25mm
J5: JST_LED_SPI_In_Index; FPC_JST_Conn_GH_4x1.25mm
J6: JST_LED_SPI_In_Major; FPC_JST_Conn_GH_4x1.25mm
J7: JST_SPI_LED_Out_Thumb; FPC_JST_Conn_GH_2x1.25mm
J8: JST_SPI_LED_Out_Index; FPC_JST_Conn_GH_2x1.25mm
J9: JST_SPI_LED_Out_Major; FPC_JST_Conn_GH_2x1.25mm
J10: JST_SPI_LED_Out_Ring; FPC_JST_Conn_GH_2x1.25mm
J11: JST_SPI_LED_Out_Little; FPC_JST_Conn_GH_2x1.25mm
J12, J13, J14, J15, J16: FSR; FPC_JST_Conn_GH_2x1.25mm
J17, J18, J19, J20, J21: Flex; FPC_JST_Conn_GH_2x1.25mm
Mosi: TestPoint_Pad_D1.0mm
U1: ICM-42688-P_I2C; FPC_ICM-42688-P2
U2: Hall Sensor DRV5023; FPC_SOT_23
hall mosi: TestPoint_Pad_D1.0mm
imu2, imu3, imu4, imu9, imu10: TestPoint_Pad_D1.0mm
imu scl: TestPoint_Pad_D1.0mm
imu sda: TestPoint_Pad_D1.0mm
sck: TestPoint_Pad_D1.0mm

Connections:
5VL: J1.23 (5V), J1.24 (5V), J2.3, J3.3, J4.3, J5.3, J6.3
+3.3V: C1.2, C2.1, C3.1, C4.1, J1.17 (3.3V), J12.2, J13.2, J14.2, J15.2, J16.2, J17.2, J18.2, J19.2, J20.2, J21.2, U1.5 (VDDIO), U1.8 (VDD), U1.12 (VDDIO), U2.1 (VCC)
/FSR_Index/TouchADC: J1.10 (FSR_INDEX), J13.1
/FSR_Little/TouchADC: J1.3 (FSR_LITTLE), J16.1
/FSR_Middle/TouchADC: J1.8 (FSR_MIDDLE), J14.1
/FSR_Ring/TouchADC: J1.5 (FSR_RING), J15.1
/FSR_Thumb/TouchADC: J1.12 (FSR_THUMB), J12.1
/FingerLED/LED_MOSI: J1.20 (MOSI), J4.1, Mosi.1
/FingerLED/LED_SCK: J1.19 (SCK), J4.2, sck.1
/Flex_Index/FlexADC: J1.9 (FLEX_INDEX), J18.1
/Flex_Little/FlexADC: J1.2 (FLEX_LITTLE), J21.1
/Flex_Middle/FlexADC: J1.6 (FLEX_MIDDLE), J19.1
/Flex_Ring/FlexADC: J1.4 (FLEX_RING), J20.1
/Flex_Thumb/FlexADC: J1.11 (FLEX_THUMB), J17.1
/Hall Captor/Hall_Captor_GPIO: J1.13 (HALL), U2.3 (Output), hall mosi.1
/IMU_1/IMU_I2C_SCL: J1.16 (SDA), U1.13 (AP_SCK), imu scl.1
/IMU_1/IMU_I2C_SDA: J1.15 (SCL), U1.14 (AP_SDA), imu sda.1
GND: C1.1, C2.2, C3.2, C4.2, J1.1 (GND), J1.7 (GND), J1.14 (GND), J1.18 (GND), J1.21 (GND), J1.22 (GND), J1.25, J2.4, J2.MP, J3.4, J3.MP, J4.4, J4.MP, J5.4, J5.MP, J6.4, J6.MP, J7.MP, J8.MP, J9.MP, J10.MP, J11.MP, J12.MP, J13.MP, J14.MP, J15.MP, J16.MP, J17.MP, J18.MP, J19.MP, J20.MP, J21.MP, U1.1 (AP_AD0), U1.6 (GND), U1.7 (RESV), U1.11 (RESV), U2.2 (GND)
unnamed: J3.1, J9.2
unnamed: J3.2, J9.1
unnamed: J5.1, J7.2
unnamed: J5.2, J7.1
unnamed: J6.1, J8.2
unnamed: J6.2, J8.1
unnamed: J2.2, J10.1
unnamed: J2.1, J10.2

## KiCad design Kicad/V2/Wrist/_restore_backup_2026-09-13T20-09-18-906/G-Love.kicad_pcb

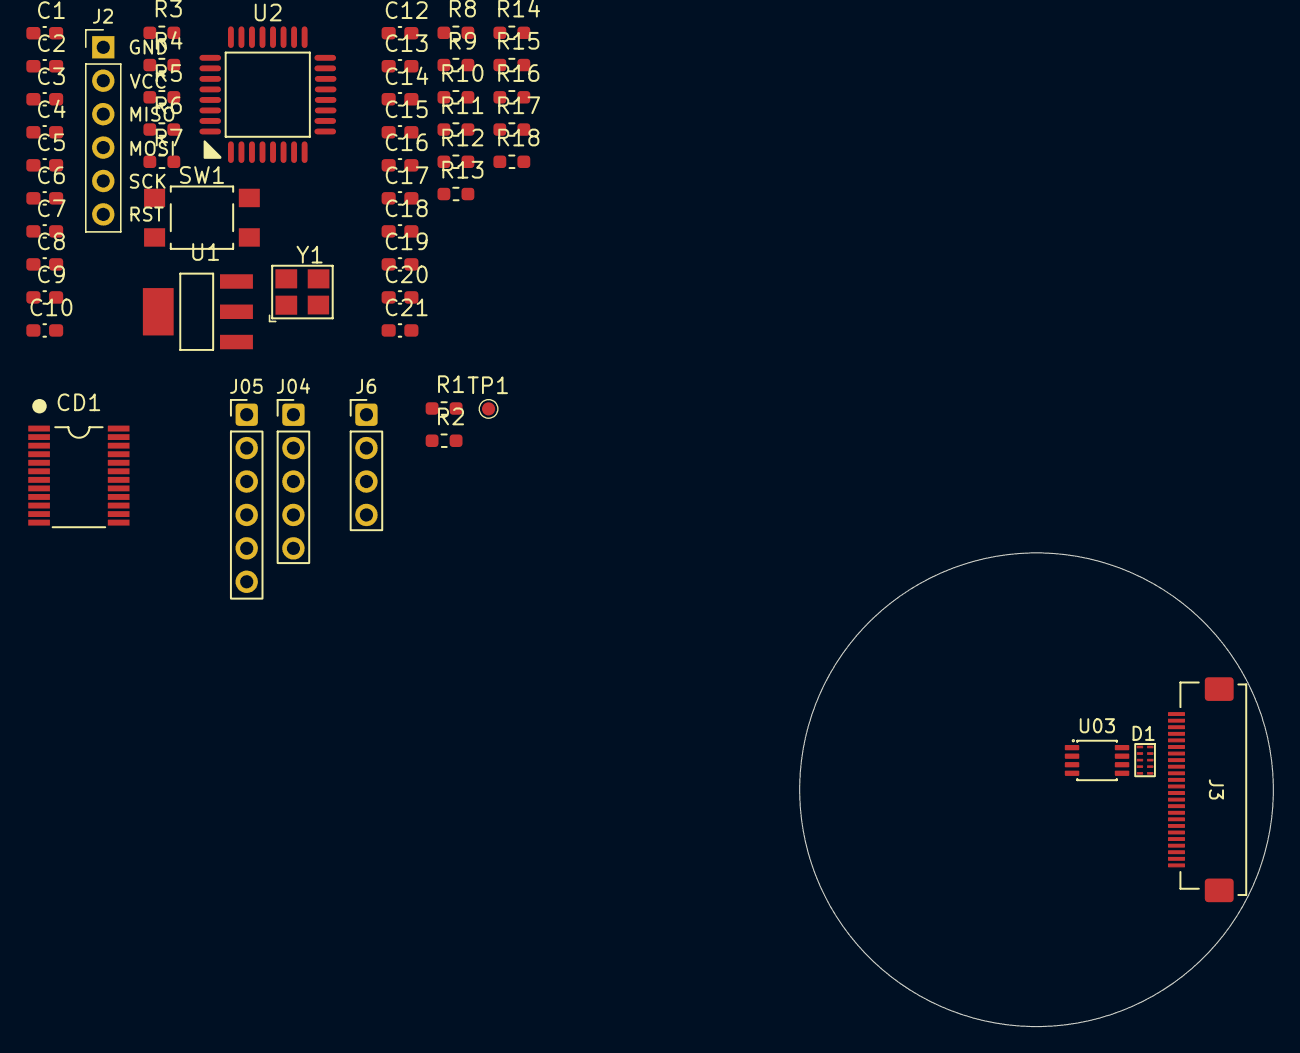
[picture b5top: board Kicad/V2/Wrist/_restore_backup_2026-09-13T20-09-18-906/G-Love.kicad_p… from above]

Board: 2 copper layers, 36.0 x 36.0 mm, 52 parts (0 on the bottom side), 34 nets, no tracks yet.

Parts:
C1, C3, C4, C5, C6, C7, C8: 100nF; Capacitor_0603
C2: 10uF; Capacitor_0603
C9, C10: 12pF; Capacitor_0603
C12, C13, C14, C15, C16, C17, C18, C19, C20, C21: 10nF; Capacitor_0603
CD1: CD4097B
D1: TVS_DIODE
J01: FPC 14
J2: PinHeader_1x06_P2.54mm_Vertical
J3: FPC_CONNECTOR_24
J04: Pinheader 5
J05: Pinheader 6
J6: Pinheader 4
R1, R2: 2.2K; Resistor_0603
R3, R9, R10, R11, R12, R13, R14, R15, R16, R17, R18: 10kΩ; Resistor_0603
R4, R5: 330R; Resistor_0603
R6, R7: 2.2kΩ; Resistor_0603
R8: 10K; Resistor_0603
SW1: SW_SPST_TL3305A
TP1: Test_point
U1: XC6206P332MR-G; AMS1117
U2: ATMega328P; ATMega328P-AU
U03: TXS0102DCUR; LVL SHIFTER TXS0102DCUR
Y1: 16MHz; Crystal_16MHz

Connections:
+3.3V: C1.1, C1.2, C2.1, C2.2, C3.1, C3.2, C4.1, C5.1, C5.2, C6.1, C6.2, C7.1, C8.1, C8.2, C9.1, C10.1, C12.2, C13.2, C14.2, C15.2, C16.2, C17.2, C18.2, C19.2, C20.2, C21.2, CD1.12 (VSS), CD1.24 (VDD), D1.3, D1.5, J2.1, J2.6, J3.3 (GNDL), J3.4 (GNDL), J3.7 (GND), J3.8 (3.3V), J3.10 (SCL), J3.11 (GND), J3.18 (GND), J3.24 (GND), J05.5, J05.6, J6.1, J6.4, R1.2, R2.2, R3.2, R6.2, R7.2, R8.2, R9.2, R10.2, R11.2, R12.2, R13.2, R14.2, R15.2, R16.2, R17.2, R18.2, TP1.1, U1.1 (GND), U1.2 (Vout), U1.3 (Vin), U2.3 (GND), U2.4 (VCC), U2.5 (GND), U2.6 (VCC), U2.18 (AVCC), U2.21 (GND), U03.2 (GND), U03.3 (VCCA), U03.5 (A1), U03.6 (OE), U03.7 (VCCB), Y1.2 (G), Y1.4 (G)
/ATmega328p/328P_ADC_MUX_INH: CD1.13 (INHIBIT), U2.26 (ADC3/PCINT11/PC3)
/ATmega328p/328P_ADC_MUX_SELECT_A: CD1.10 (A), U2.25 (ADC2/PCINT10/PC2)
/ATmega328p/328P_ADC_MUX_SELECT_B: CD1.11 (B), U2.23 (ADC0/PCINT8/PC0)
/ATmega328p/328P_ADC_MUX_SELECT_C: CD1.14 (C), U2.24 (ADC1/PCINT9/PC1)
/ATmega328p/328P_ADC_X_OUT: CD1.1 (X_OutIn), U2.22 (ADC7)
/ATmega328p/328P_ADC_Y_OUT: CD1.17 (Y_OutIn), U2.19 (ADC6)
/ATmega328p/328P_I2C_IMU_SCL: R2.1, R6.1, U2.28 (SCL/ADC5/PCINT13/PC5), U03.4 (A2)
/ATmega328p/328P_I2C_IMU_SDA: R1.1, R7.1, U2.27 (SDA/ADC4/PSCINT12/PC4), U03.1 (B2)
/ATmega328p/MCU_328P_RESET: J2.4, R3.1, SW1.2, U2.29 (~RESET/PCINT14/PC6)
/ATmega328p/MISO_BOOT_328P: D1.1, J2.2, J3.5 (MOSI), R4.2
/ATmega328p/MOSI_BOOT_328P: J2.3, U2.16 (MISO/PCINT4/PB4)
/ATmega328p/SCK_BOOT_328P: D1.2, J2.5, J3.6 (SCK), R5.2
/FingerTip Modules/FingerTip_I2C_SCL: J05.1, J6.2
/FingerTip Modules/FingerTip_I2C_SDA: J05.2, J6.3
/Hand_Captors/hand_captors/FLEX_INDEX_IN: C15.1, CD1.8 (X_1), J3.16 (FLEX_INDEX), R12.1
/Hand_Captors/hand_captors/FLEX_LITTLE_IN: C21.1, CD1.5 (X_4), J3.23 (FLEX_LITTLE), R18.1
/Hand_Captors/hand_captors/FLEX_MIDDLE_IN: C17.1, CD1.7 (X_2), J3.19 (FLEX_MIDDLE), R14.1
/Hand_Captors/hand_captors/FLEX_RING_IN: C19.1, CD1.6 (X_3), J3.21 (FLEX_RING), R16.1
/Hand_Captors/hand_captors/FLEX_THUMB_IN: C13.1, CD1.9 (X_0), J3.14 (FLEX_THUMB), R10.1
/Hand_Captors/hand_captors/FORCE_INDEX_IN: C14.1, CD1.22 (Y_1), J3.15 (FSR_INDEX), R11.1
/Hand_Captors/hand_captors/FORCE_LITTLE_IN: C20.1, CD1.19 (Y_4), J3.22 (FORCE_LITTLE), R17.1
/Hand_Captors/hand_captors/FORCE_MIDDLE_IN: C16.1, CD1.21 (Y_2), J3.17 (FSR_MIDDLE), R13.1
/Hand_Captors/hand_captors/FORCE_RING_IN: C18.1, CD1.20 (Y_3), J3.20 (FORCE_RING), R15.1
/Hand_Captors/hand_captors/FORCE_THUMB_IN: C12.1, CD1.23 (Y_0), J3.13 (FSR_THUMB), R9.1
/Hand_Captors/hand_captors/HALL_IN: CD1.18 (Y_5), J3.12 (SW_HALL), R8.1
unnamed: C7.2, SW1.1
unnamed: C4.2, U2.20 (AREF)
unnamed: R4.1, U2.15 (OC2A/MOSI/PCINT3/PB3)
unnamed: R5.1, U2.17 (SCK/PCINT5/PB5)
unnamed: C9.2, U2.7 (XTAL1/TOSC1/PCINT6/PB6), Y1.1
unnamed: C10.2, U2.8 (XTAL2/TOSC2/PCINT7/PB7), Y1.3
unnamed: D1.4, J3.9 (SDA), U03.8 (B1)
VCCL: J3.1 (VCCL), J3.2 (VCCL)
